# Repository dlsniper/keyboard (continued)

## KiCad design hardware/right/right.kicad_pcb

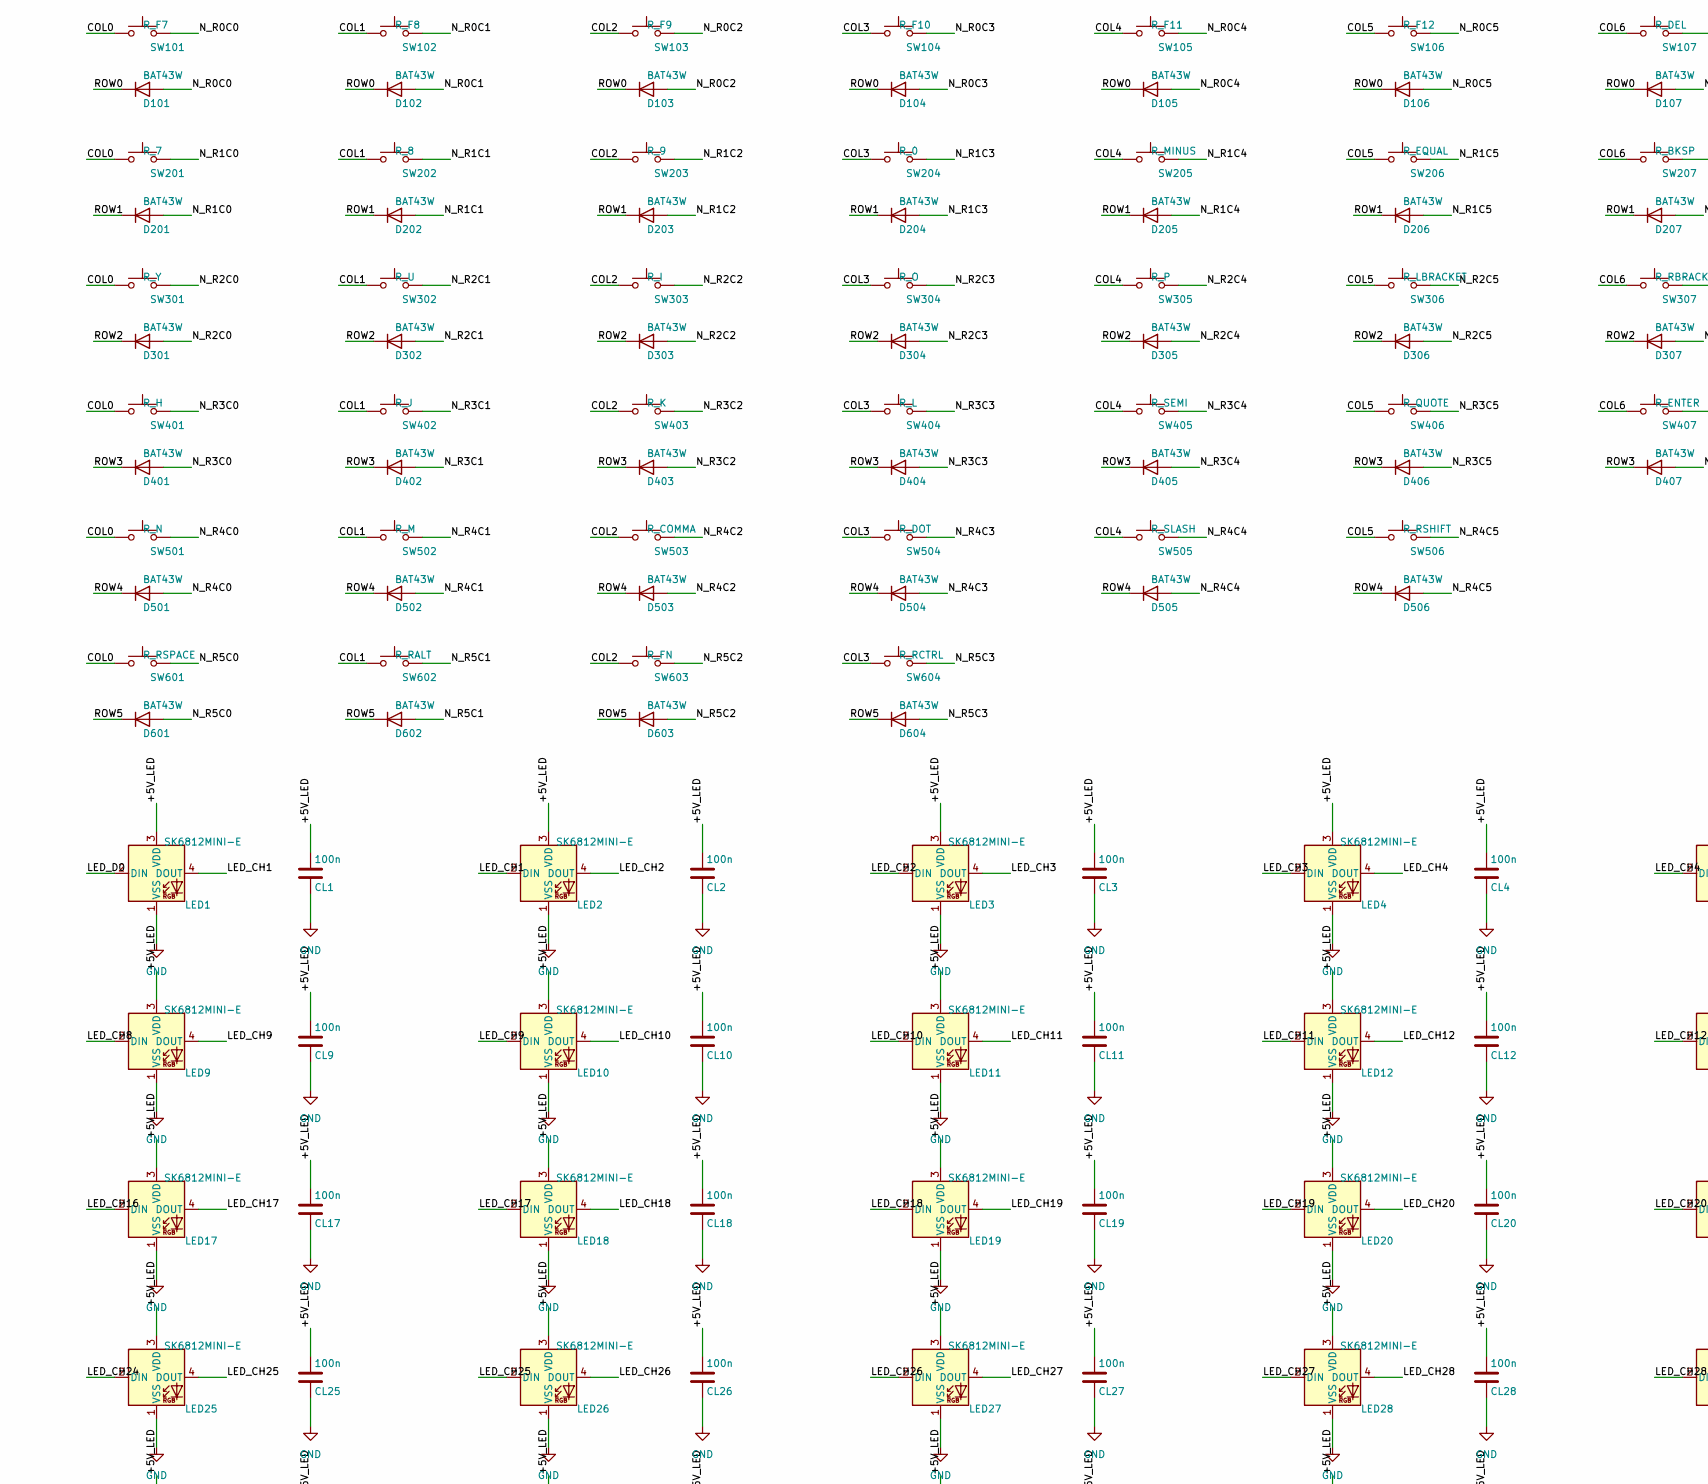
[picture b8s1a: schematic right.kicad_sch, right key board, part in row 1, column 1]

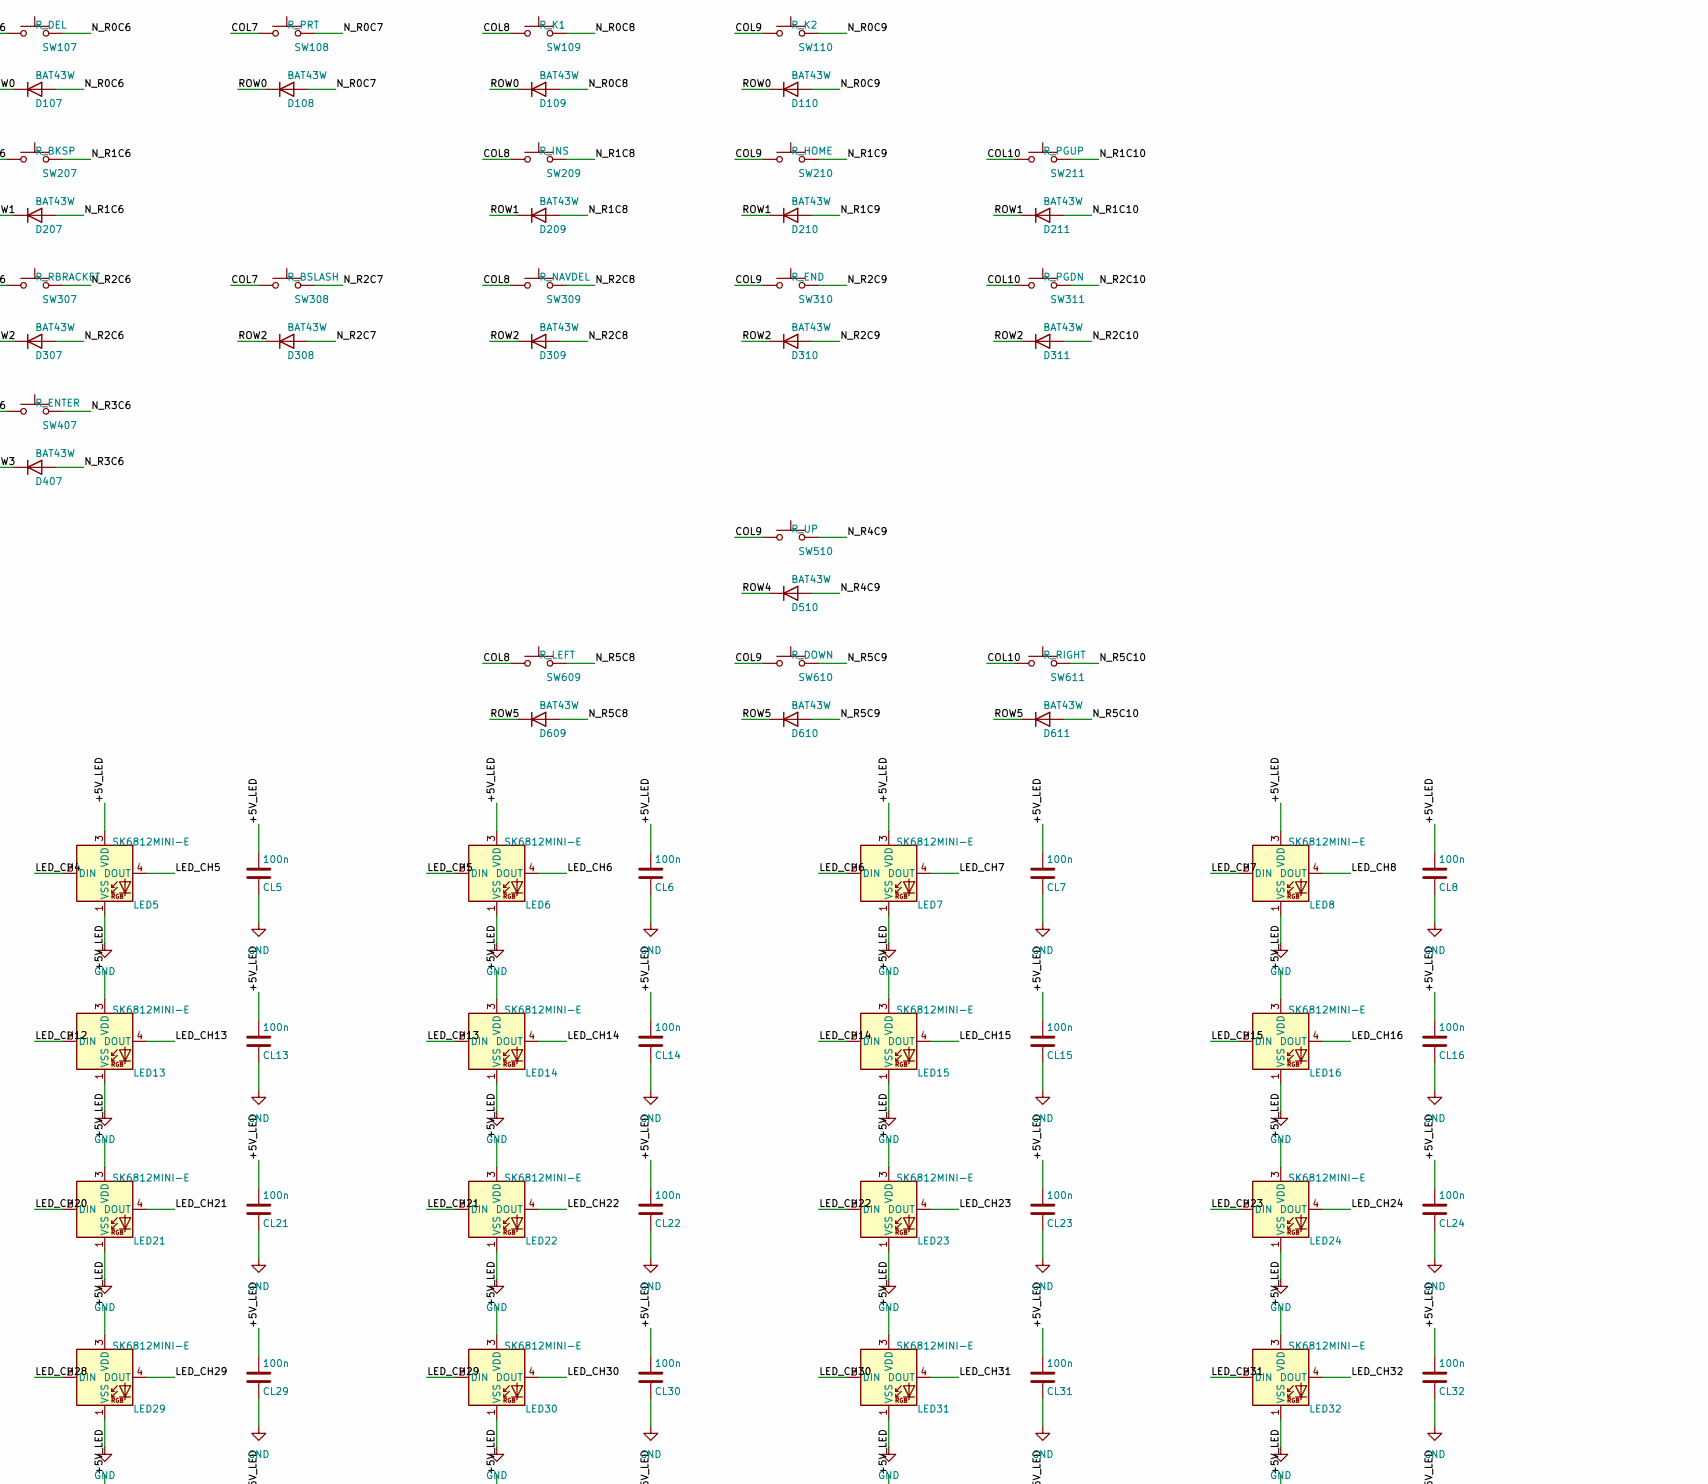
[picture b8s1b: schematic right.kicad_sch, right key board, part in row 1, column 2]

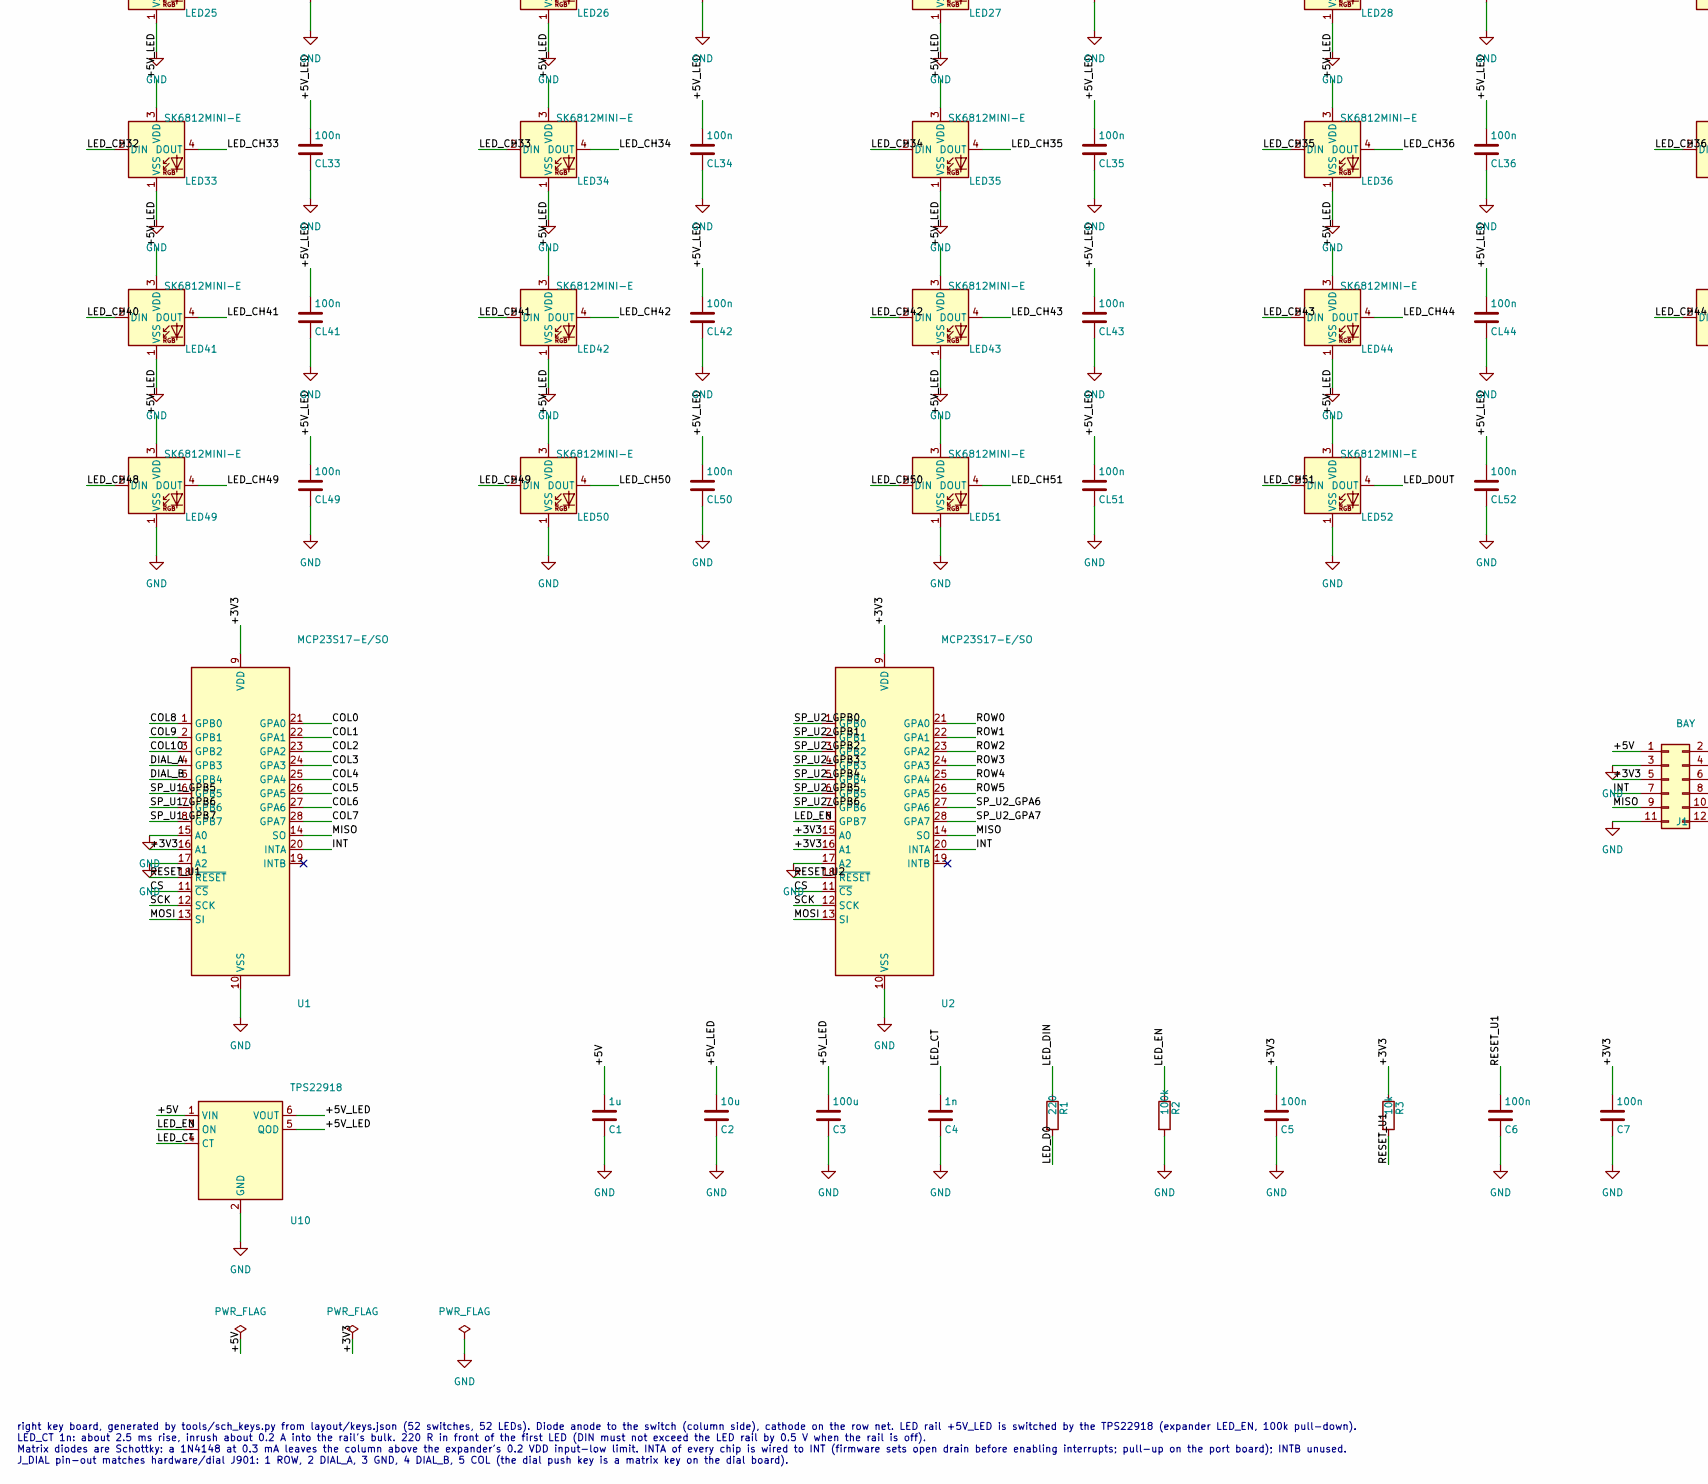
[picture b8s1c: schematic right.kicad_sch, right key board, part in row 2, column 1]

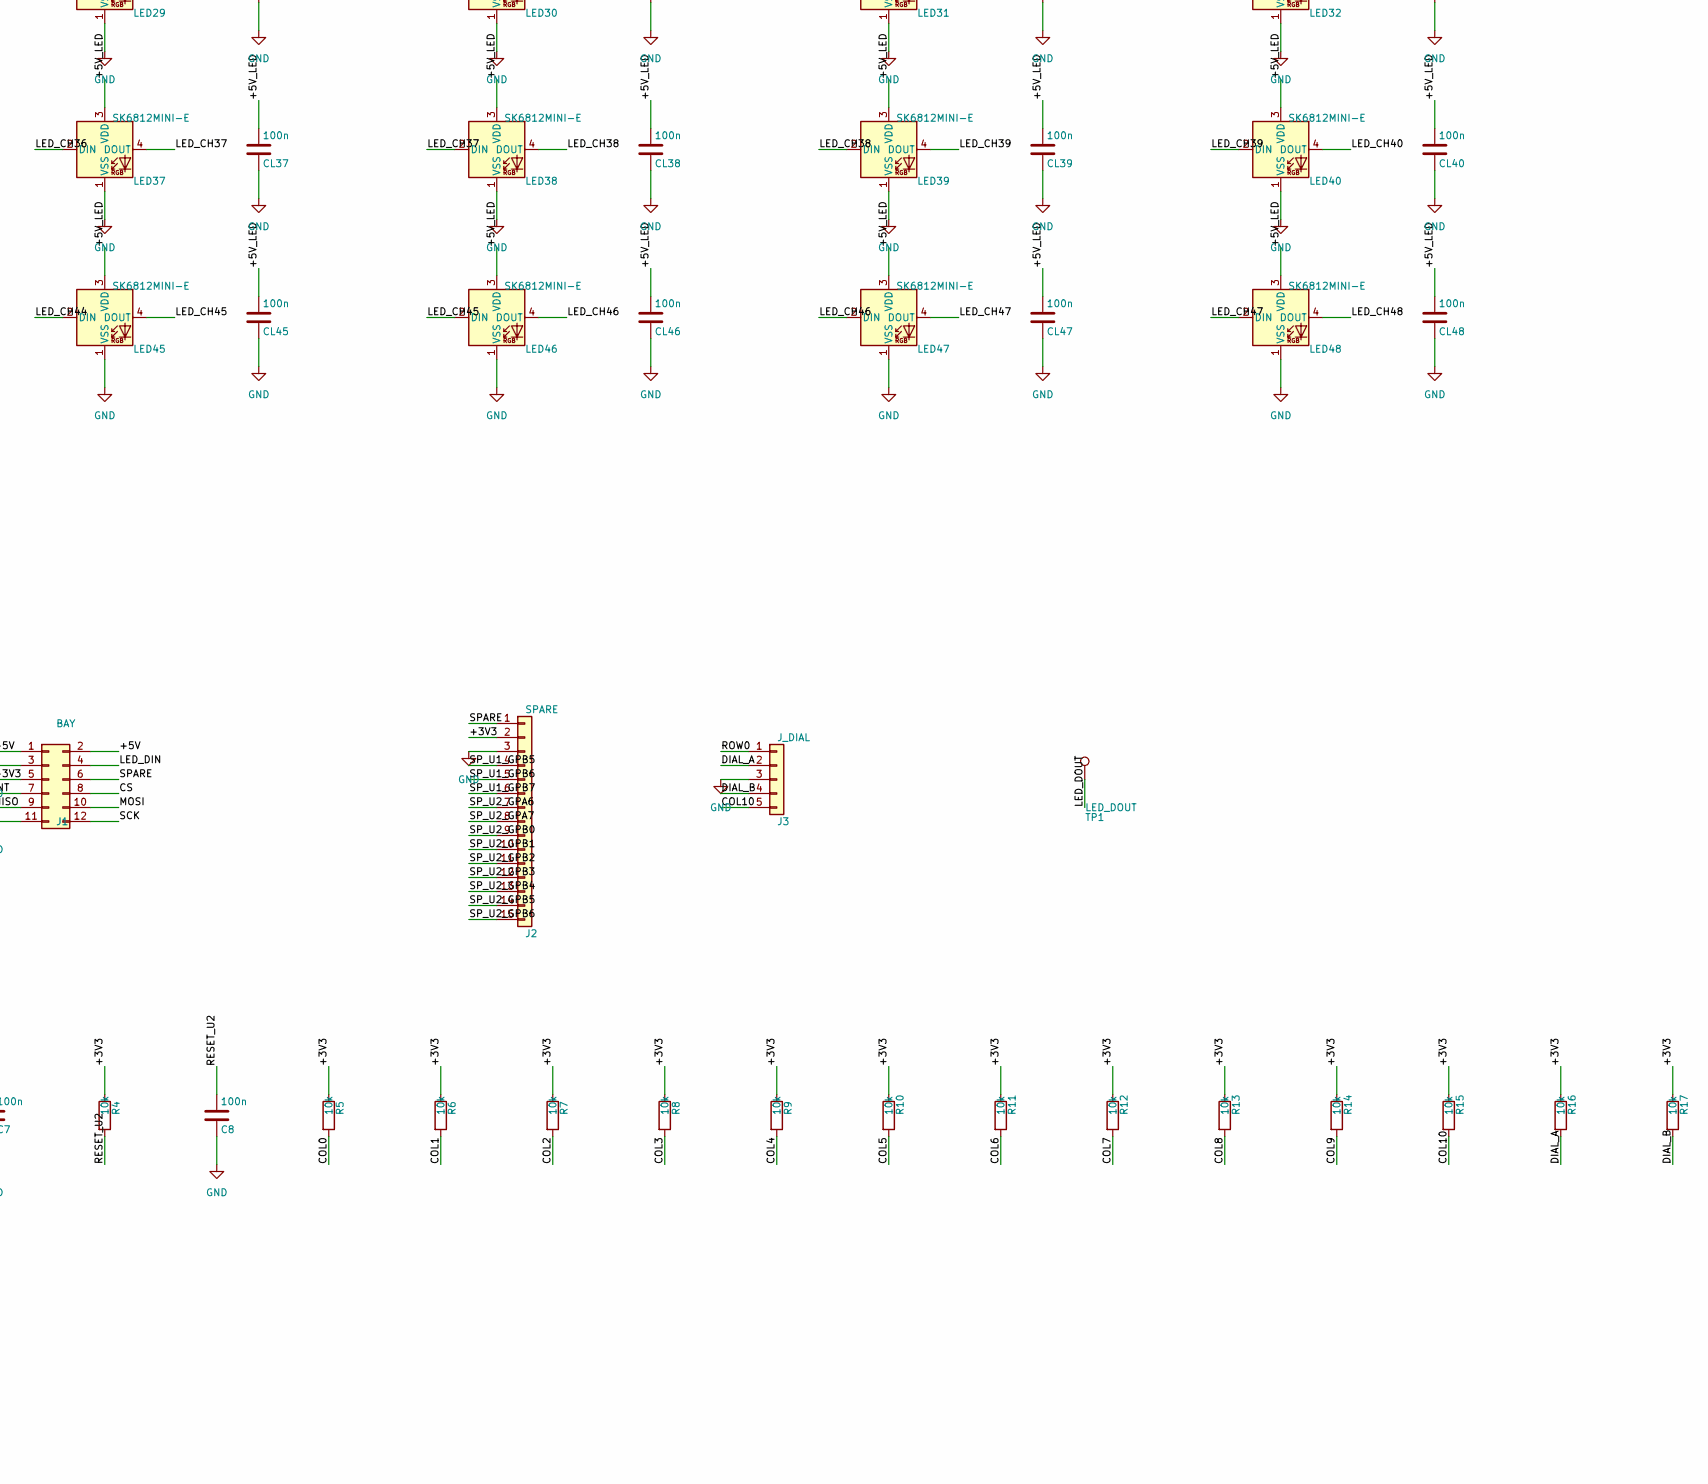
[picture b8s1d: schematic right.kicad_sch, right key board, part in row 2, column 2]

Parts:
C1: 1u; C_0805_2012Metric_Pad1.18x1.45mm_HandSolder; Voltage 16V
C2: 10u; C_0805_2012Metric_Pad1.18x1.45mm_HandSolder; Voltage 16V
C3: 100u; C_1210_3225Metric_Pad1.33x2.70mm_HandSolder; Voltage 10V
C4: 1n; C_0805_2012Metric_Pad1.18x1.45mm_HandSolder; Voltage 16V
C5, C6, C7, C8: 100n; C_0805_2012Metric_Pad1.18x1.45mm_HandSolder; Voltage 16V
CL1, CL2, CL3, CL4, CL5, CL6, CL7, CL8, CL9, CL10, CL11, CL12, CL13, CL14, CL15, CL16, CL17, CL18, CL19, CL20, CL21, CL22, CL23, CL24, CL25, CL26, CL27, CL28, CL29, CL30, CL31, CL32, CL33, CL34, CL35, CL36, CL37, CL38, CL39, CL40, CL41, CL42, CL43, CL44, CL45, CL46, CL47, CL48, CL49, CL50, CL51, CL52: 100n; C_0805_2012Metric_Pad1.18x1.45mm_HandSolder; Voltage 16V
D101, D102, D103, D104, D105, D106, D107, D108, D109, D110, D201, D202, D203, D204, D205, D206, D207, D209, D210, D211, D301, D302, D303, D304, D305, D306, D307, D308, D309, D310, D311, D401, D402, D403, D404, D405, D406, D407, D501, D502, D503, D504, D505, D506, D510, D601, D602, D603, D604, D609, D610, D611: BAT43W; D_SOD-123; MPN Schottky, SOD-123: BAT43W (VF 0.33 V ma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
J1: BAY; PinHeader_2x06_P2.54mm_Vertical; MPN generic 2x6 2.54 mm pin header
J2: SPARE; PinHeader_1x15_P2.54mm_Vertical; MPN generic 1xN 2.54 mm pin header
J3: J_DIAL; JST_GH_SM05B-GHS-TB_1x05-1MP_P1.25mm_Horizontal; MPN JST SM05B-GHS-TB
LED1, LED2, LED3, LED4, LED5, LED6, LED7, LED8, LED9, LED10, LED11, LED12, LED13, LED14, LED15, LED16, LED17, LED18, LED19, LED20, LED21, LED22, LED23, LED24, LED25, LED26, LED27, LED28, LED29, LED30, LED31, LED32, LED33, LED34, LED35, LED36, LED37, LED38, LED39, LED40, LED41, LED42, LED43, LED44, LED45, LED46, LED47, LED48, LED49, LED50, LED51, LED52: SK6812MINI-E; LED_SK6812MINI-E_3.2x2.8mm_P1.5mm_ReverseMount; MPN SK6812MINI-E
R1: 220; R_0805_2012Metric_Pad1.20x1.40mm_HandSolder; Tolerance 1%
R2: 100k; R_0805_2012Metric_Pad1.20x1.40mm_HandSolder; Tolerance 1%
R3, R4, R5, R6, R7, R8, R9, R10, R11, R12, R13, R14, R15, R16, R17: 10k; R_0805_2012Metric_Pad1.20x1.40mm_HandSolder; Tolerance 1%
SW101: R_F7; SW_Hotswap_Kailh_MX_1.00u; MPN Kailh CPG151101S11 hotswap socket
SW102: R_F8; SW_Hotswap_Kailh_MX_1.00u; MPN Kailh CPG151101S11 hotswap socket
SW103: R_F9; SW_Hotswap_Kailh_MX_1.00u; MPN Kailh CPG151101S11 hotswap socket
SW104: R_F10; SW_Hotswap_Kailh_MX_1.00u; MPN Kailh CPG151101S11 hotswap socket
SW105: R_F11; SW_Hotswap_Kailh_MX_1.00u; MPN Kailh CPG151101S11 hotswap socket
SW106: R_F12; SW_Hotswap_Kailh_MX_1.00u; MPN Kailh CPG151101S11 hotswap socket
SW107: R_DEL; SW_Hotswap_Kailh_MX_1.00u; MPN Kailh CPG151101S11 hotswap socket
SW108: R_PRT; SW_Hotswap_Kailh_MX_1.00u; MPN Kailh CPG151101S11 hotswap socket
SW109: R_K1; SW_Hotswap_Kailh_MX_1.00u; MPN Kailh CPG151101S11 hotswap socket
SW110: R_K2; SW_Hotswap_Kailh_MX_1.00u; MPN Kailh CPG151101S11 hotswap socket
SW201: R_7; SW_Hotswap_Kailh_MX_1.00u; MPN Kailh CPG151101S11 hotswap socket
SW202: R_8; SW_Hotswap_Kailh_MX_1.00u; MPN Kailh CPG151101S11 hotswap socket
SW203: R_9; SW_Hotswap_Kailh_MX_1.00u; MPN Kailh CPG151101S11 hotswap socket
SW204: R_0; SW_Hotswap_Kailh_MX_1.00u; MPN Kailh CPG151101S11 hotswap socket
SW205: R_MINUS; SW_Hotswap_Kailh_MX_1.00u; MPN Kailh CPG151101S11 hotswap socket
SW206: R_EQUAL; SW_Hotswap_Kailh_MX_1.00u; MPN Kailh CPG151101S11 hotswap socket
SW207: R_BKSP; SW_Hotswap_Kailh_MX_2.00u; MPN Kailh CPG151101S11 hotswap socket
SW209: R_INS; SW_Hotswap_Kailh_MX_1.00u; MPN Kailh CPG151101S11 hotswap socket
SW210: R_HOME; SW_Hotswap_Kailh_MX_1.00u; MPN Kailh CPG151101S11 hotswap socket
SW211: R_PGUP; SW_Hotswap_Kailh_MX_1.00u; MPN Kailh CPG151101S11 hotswap socket
SW301: R_Y; SW_Hotswap_Kailh_MX_1.00u; MPN Kailh CPG151101S11 hotswap socket
SW302: R_U; SW_Hotswap_Kailh_MX_1.00u; MPN Kailh CPG151101S11 hotswap socket
SW303: R_I; SW_Hotswap_Kailh_MX_1.00u; MPN Kailh CPG151101S11 hotswap socket
SW304: R_O; SW_Hotswap_Kailh_MX_1.00u; MPN Kailh CPG151101S11 hotswap socket
SW305: R_P; SW_Hotswap_Kailh_MX_1.00u; MPN Kailh CPG151101S11 hotswap socket
SW306: R_LBRACKET; SW_Hotswap_Kailh_MX_1.00u; MPN Kailh CPG151101S11 hotswap socket
SW307: R_RBRACKET; SW_Hotswap_Kailh_MX_1.00u; MPN Kailh CPG151101S11 hotswap socket
SW308: R_BSLASH; SW_Hotswap_Kailh_MX_1.50u; MPN Kailh CPG151101S11 hotswap socket
SW309: R_NAVDEL; SW_Hotswap_Kailh_MX_1.00u; MPN Kailh CPG151101S11 hotswap socket
SW310: R_END; SW_Hotswap_Kailh_MX_1.00u; MPN Kailh CPG151101S11 hotswap socket
SW311: R_PGDN; SW_Hotswap_Kailh_MX_1.00u; MPN Kailh CPG151101S11 hotswap socket
SW401: R_H; SW_Hotswap_Kailh_MX_1.00u; MPN Kailh CPG151101S11 hotswap socket
SW402: R_J; SW_Hotswap_Kailh_MX_1.00u; MPN Kailh CPG151101S11 hotswap socket
SW403: R_K; SW_Hotswap_Kailh_MX_1.00u; MPN Kailh CPG151101S11 hotswap socket
SW404: R_L; SW_Hotswap_Kailh_MX_1.00u; MPN Kailh CPG151101S11 hotswap socket
SW405: R_SEMI; SW_Hotswap_Kailh_MX_1.00u; MPN Kailh CPG151101S11 hotswap socket
SW406: R_QUOTE; SW_Hotswap_Kailh_MX_1.00u; MPN Kailh CPG151101S11 hotswap socket
SW407: R_ENTER; SW_Hotswap_Kailh_MX_2.25u; MPN Kailh CPG151101S11 hotswap socket
SW501: R_N; SW_Hotswap_Kailh_MX_1.00u; MPN Kailh CPG151101S11 hotswap socket
SW502: R_M; SW_Hotswap_Kailh_MX_1.00u; MPN Kailh CPG151101S11 hotswap socket
SW503: R_COMMA; SW_Hotswap_Kailh_MX_1.00u; MPN Kailh CPG151101S11 hotswap socket
SW504: R_DOT; SW_Hotswap_Kailh_MX_1.00u; MPN Kailh CPG151101S11 hotswap socket
SW505: R_SLASH; SW_Hotswap_Kailh_MX_1.00u; MPN Kailh CPG151101S11 hotswap socket
SW506: R_RSHIFT; SW_Hotswap_Kailh_MX_2.75u; MPN Kailh CPG151101S11 hotswap socket
SW510: R_UP; SW_Hotswap_Kailh_MX_1.00u; MPN Kailh CPG151101S11 hotswap socket
SW601: R_RSPACE; SW_Hotswap_Kailh_MX_2.75u; MPN Kailh CPG151101S11 hotswap socket
SW602: R_RALT; SW_Hotswap_Kailh_MX_1.75u; MPN Kailh CPG151101S11 hotswap socket
SW603: R_FN; SW_Hotswap_Kailh_MX_1.75u; MPN Kailh CPG151101S11 hotswap socket
SW604: R_RCTRL; SW_Hotswap_Kailh_MX_1.50u; MPN Kailh CPG151101S11 hotswap socket
SW609: R_LEFT; SW_Hotswap_Kailh_MX_1.00u; MPN Kailh CPG151101S11 hotswap socket
SW610: R_DOWN; SW_Hotswap_Kailh_MX_1.00u; MPN Kailh CPG151101S11 hotswap socket
SW611: R_RIGHT; SW_Hotswap_Kailh_MX_1.00u; MPN Kailh CPG151101S11 hotswap socket
TP1: LED_DOUT; TestPoint_Pad_D1.5mm
U1, U2: MCP23S17-E/SO; SOIC-28W_7.5x17.9mm_P1.27mm; MPN Microchip MCP23S17-E/SO
U10: TPS22918; TI_SOT-23-6_DBV0006A; MPN TI TPS22918DBVR

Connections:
/+3V3: C5.1, C7.1, J1.5, J2.2, R3.1, R4.1, R5.1, R6.1, R7.1, R8.1, R9.1, R10.1, R11.1, R12.1, R13.1, R14.1, R15.1, R16.1, R17.1, U1.9 (VDD), U1.16 (A1), U2.9 (VDD), U2.15 (A0), U2.16 (A1)
/+5V: C1.1, J1.1, J1.2, U10.1 (VIN)
/+5V_LED: C2.1, C3.1, CL1.1, CL2.1, CL3.1, CL4.1, CL5.1, CL6.1, CL7.1, CL8.1, CL9.1, CL10.1, CL11.1, CL12.1, CL13.1, CL14.1, CL15.1, CL16.1, CL17.1, CL18.1, CL19.1, CL20.1, CL21.1, CL22.1, CL23.1, CL24.1, CL25.1, CL26.1, CL27.1, CL28.1, CL29.1, CL30.1, CL31.1, CL32.1, CL33.1, CL34.1, CL35.1, CL36.1, CL37.1, CL38.1, CL39.1, CL40.1, CL41.1, CL42.1, CL43.1, CL44.1, CL45.1, CL46.1, CL47.1, CL48.1, CL49.1, CL50.1, CL51.1, CL52.1, LED1.3 (VDD), LED2.3 (VDD), LED3.3 (VDD), LED4.3 (VDD), LED5.3 (VDD), LED6.3 (VDD), LED7.3 (VDD), LED8.3 (VDD), LED9.3 (VDD), LED10.3 (VDD), LED11.3 (VDD), LED12.3 (VDD), LED13.3 (VDD), LED14.3 (VDD), LED15.3 (VDD), LED16.3 (VDD), LED17.3 (VDD), LED18.3 (VDD), LED19.3 (VDD), LED20.3 (VDD), LED21.3 (VDD), LED22.3 (VDD), LED23.3 (VDD), LED24.3 (VDD), LED25.3 (VDD), LED26.3 (VDD), LED27.3 (VDD), LED28.3 (VDD), LED29.3 (VDD), LED30.3 (VDD), LED31.3 (VDD), LED32.3 (VDD), LED33.3 (VDD), LED34.3 (VDD), LED35.3 (VDD), LED36.3 (VDD), LED37.3 (VDD), LED38.3 (VDD), LED39.3 (VDD), LED40.3 (VDD), LED41.3 (VDD), LED42.3 (VDD), LED43.3 (VDD), LED44.3 (VDD), LED45.3 (VDD), LED46.3 (VDD), LED47.3 (VDD), LED48.3 (VDD), LED49.3 (VDD), LED50.3 (VDD), LED51.3 (VDD), LED52.3 (VDD), U10.5 (QOD), U10.6 (VOUT)
/COL0: R5.2, SW101.1, SW201.1, SW301.1, SW401.1, SW501.1, SW601.1, U1.21 (GPA0)
/COL1: R6.2, SW102.1, SW202.1, SW302.1, SW402.1, SW502.1, SW602.1, U1.22 (GPA1)
/COL2: R7.2, SW103.1, SW203.1, SW303.1, SW403.1, SW503.1, SW603.1, U1.23 (GPA2)
/COL3: R8.2, SW104.1, SW204.1, SW304.1, SW404.1, SW504.1, SW604.1, U1.24 (GPA3)
/COL4: R9.2, SW105.1, SW205.1, SW305.1, SW405.1, SW505.1, U1.25 (GPA4)
/COL5: R10.2, SW106.1, SW206.1, SW306.1, SW406.1, SW506.1, U1.26 (GPA5)
/COL6: R11.2, SW107.1, SW207.1, SW307.1, SW407.1, U1.27 (GPA6)
/COL7: R12.2, SW108.1, SW308.1, U1.28 (GPA7)
/COL8: R13.2, SW109.1, SW209.1, SW309.1, SW609.1, U1.1 (GPB0)
/COL9: R14.2, SW110.1, SW210.1, SW310.1, SW510.1, SW610.1, U1.2 (GPB1)
/COL10: J3.5, R15.2, SW211.1, SW311.1, SW611.1, U1.3 (GPB2)
/CS: J1.8, U1.11 (~CS), U2.11 (~CS)
/DIAL_A: J3.2, R16.2, U1.4 (GPB3)
/DIAL_B: J3.4, R17.2, U1.5 (GPB4)
/INT: J1.7, U1.20 (INTA), U2.20 (INTA)
/LED_CH1: LED1.4 (DOUT), LED2.2 (DIN)
/LED_CH2: LED2.4 (DOUT), LED3.2 (DIN)
/LED_CH3: LED3.4 (DOUT), LED4.2 (DIN)
/LED_CH4: LED4.4 (DOUT), LED5.2 (DIN)
/LED_CH5: LED5.4 (DOUT), LED6.2 (DIN)
/LED_CH6: LED6.4 (DOUT), LED7.2 (DIN)
/LED_CH7: LED7.4 (DOUT), LED8.2 (DIN)
/LED_CH8: LED8.4 (DOUT), LED9.2 (DIN)
/LED_CH9: LED9.4 (DOUT), LED10.2 (DIN)
/LED_CH10: LED10.4 (DOUT), LED11.2 (DIN)
/LED_CH11: LED11.4 (DOUT), LED12.2 (DIN)
/LED_CH12: LED12.4 (DOUT), LED13.2 (DIN)
/LED_CH13: LED13.4 (DOUT), LED14.2 (DIN)
/LED_CH14: LED14.4 (DOUT), LED15.2 (DIN)
/LED_CH15: LED15.4 (DOUT), LED16.2 (DIN)
/LED_CH16: LED16.4 (DOUT), LED17.2 (DIN)
/LED_CH17: LED17.4 (DOUT), LED18.2 (DIN)
/LED_CH18: LED18.4 (DOUT), LED19.2 (DIN)
/LED_CH19: LED19.4 (DOUT), LED20.2 (DIN)
/LED_CH20: LED20.4 (DOUT), LED21.2 (DIN)
/LED_CH21: LED21.4 (DOUT), LED22.2 (DIN)
/LED_CH22: LED22.4 (DOUT), LED23.2 (DIN)
/LED_CH23: LED23.4 (DOUT), LED24.2 (DIN)
/LED_CH24: LED24.4 (DOUT), LED25.2 (DIN)
/LED_CH25: LED25.4 (DOUT), LED26.2 (DIN)
/LED_CH26: LED26.4 (DOUT), LED27.2 (DIN)
/LED_CH27: LED27.4 (DOUT), LED28.2 (DIN)
/LED_CH28: LED28.4 (DOUT), LED29.2 (DIN)
/LED_CH29: LED29.4 (DOUT), LED30.2 (DIN)
/LED_CH30: LED30.4 (DOUT), LED31.2 (DIN)
/LED_CH31: LED31.4 (DOUT), LED32.2 (DIN)
/LED_CH32: LED32.4 (DOUT), LED33.2 (DIN)
/LED_CH33: LED33.4 (DOUT), LED34.2 (DIN)
/LED_CH34: LED34.4 (DOUT), LED35.2 (DIN)
/LED_CH35: LED35.4 (DOUT), LED36.2 (DIN)
/LED_CH36: LED36.4 (DOUT), LED37.2 (DIN)
/LED_CH37: LED37.4 (DOUT), LED38.2 (DIN)
/LED_CH38: LED38.4 (DOUT), LED39.2 (DIN)
/LED_CH39: LED39.4 (DOUT), LED40.2 (DIN)
/LED_CH40: LED40.4 (DOUT), LED41.2 (DIN)
/LED_CH41: LED41.4 (DOUT), LED42.2 (DIN)
/LED_CH42: LED42.4 (DOUT), LED43.2 (DIN)
/LED_CH43: LED43.4 (DOUT), LED44.2 (DIN)
/LED_CH44: LED44.4 (DOUT), LED45.2 (DIN)
/LED_CH45: LED45.4 (DOUT), LED46.2 (DIN)
/LED_CH46: LED46.4 (DOUT), LED47.2 (DIN)
/LED_CH47: LED47.4 (DOUT), LED48.2 (DIN)
/LED_CH48: LED48.4 (DOUT), LED49.2 (DIN)
/LED_CH49: LED49.4 (DOUT), LED50.2 (DIN)
/LED_CH50: LED50.4 (DOUT), LED51.2 (DIN)
/LED_CH51: LED51.4 (DOUT), LED52.2 (DIN)
/LED_CT: C4.1, U10.4 (CT)
/LED_D0: LED1.2 (DIN), R1.2
/LED_DIN: J1.4, R1.1
/LED_DOUT: LED52.4 (DOUT), TP1.1
/LED_EN: R2.1, U2.8 (GPB7), U10.3 (ON)
/MISO: J1.9, U1.14 (SO), U2.14 (SO)
/MOSI: J1.10, U1.13 (SI), U2.13 (SI)
/N_R0C0: D101.2 (A), SW101.2
/N_R0C1: D102.2 (A), SW102.2
/N_R0C2: D103.2 (A), SW103.2
/N_R0C3: D104.2 (A), SW104.2
/N_R0C4: D105.2 (A), SW105.2
/N_R0C5: D106.2 (A), SW106.2
/N_R0C6: D107.2 (A), SW107.2
/N_R0C7: D108.2 (A), SW108.2
/N_R0C8: D109.2 (A), SW109.2
/N_R0C9: D110.2 (A), SW110.2
/N_R1C0: D201.2 (A), SW201.2
/N_R1C1: D202.2 (A), SW202.2
/N_R1C2: D203.2 (A), SW203.2
/N_R1C3: D204.2 (A), SW204.2
/N_R1C4: D205.2 (A), SW205.2
/N_R1C5: D206.2 (A), SW206.2
/N_R1C6: D207.2 (A), SW207.2
/N_R1C8: D209.2 (A), SW209.2
/N_R1C9: D210.2 (A), SW210.2
/N_R1C10: D211.2 (A), SW211.2
/N_R2C0: D301.2 (A), SW301.2
/N_R2C1: D302.2 (A), SW302.2
/N_R2C2: D303.2 (A), SW303.2
/N_R2C3: D304.2 (A), SW304.2
/N_R2C4: D305.2 (A), SW305.2
/N_R2C5: D306.2 (A), SW306.2
/N_R2C6: D307.2 (A), SW307.2
/N_R2C7: D308.2 (A), SW308.2
/N_R2C8: D309.2 (A), SW309.2
/N_R2C9: D310.2 (A), SW310.2
/N_R2C10: D311.2 (A), SW311.2
/N_R3C0: D401.2 (A), SW401.2
/N_R3C1: D402.2 (A), SW402.2
/N_R3C2: D403.2 (A), SW403.2
/N_R3C3: D404.2 (A), SW404.2
/N_R3C4: D405.2 (A), SW405.2
/N_R3C5: D406.2 (A), SW406.2
/N_R3C6: D407.2 (A), SW407.2
/N_R4C0: D501.2 (A), SW501.2
/N_R4C1: D502.2 (A), SW502.2
/N_R4C2: D503.2 (A), SW503.2
/N_R4C3: D504.2 (A), SW504.2
/N_R4C4: D505.2 (A), SW505.2
/N_R4C5: D506.2 (A), SW506.2
/N_R4C9: D510.2 (A), SW510.2
/N_R5C0: D601.2 (A), SW601.2
/N_R5C1: D602.2 (A), SW602.2
/N_R5C2: D603.2 (A), SW603.2
/N_R5C3: D604.2 (A), SW604.2
/N_R5C8: D609.2 (A), SW609.2
/N_R5C9: D610.2 (A), SW610.2
/N_R5C10: D611.2 (A), SW611.2
/RESET_U1: C6.1, R3.2, U1.18 (~RESET)
/RESET_U2: C8.1, R4.2, U2.18 (~RESET)
/ROW0: D101.1 (K), D102.1 (K), D103.1 (K), D104.1 (K), D105.1 (K), D106.1 (K), D107.1 (K), D108.1 (K), D109.1 (K), D110.1 (K), J3.1, U2.21 (GPA0)
/ROW1: D201.1 (K), D202.1 (K), D203.1 (K), D204.1 (K), D205.1 (K), D206.1 (K), D207.1 (K), D209.1 (K), D210.1 (K), D211.1 (K), U2.22 (GPA1)
/ROW2: D301.1 (K), D302.1 (K), D303.1 (K), D304.1 (K), D305.1 (K), D306.1 (K), D307.1 (K), D308.1 (K), D309.1 (K), D310.1 (K), D311.1 (K), U2.23 (GPA2)
/ROW3: D401.1 (K), D402.1 (K), D403.1 (K), D404.1 (K), D405.1 (K), D406.1 (K), D407.1 (K), U2.24 (GPA3)
/ROW4: D501.1 (K), D502.1 (K), D503.1 (K), D504.1 (K), D505.1 (K), D506.1 (K), D510.1 (K), U2.25 (GPA4)
/ROW5: D601.1 (K), D602.1 (K), D603.1 (K), D604.1 (K), D609.1 (K), D610.1 (K), D611.1 (K), U2.26 (GPA5)
/SCK: J1.12, U1.12 (SCK), U2.12 (SCK)
/SPARE: J1.6, J2.1
/SP_U1_GPB5: J2.4, U1.6 (GPB5)
/SP_U1_GPB6: J2.5, U1.7 (GPB6)
/SP_U1_GPB7: J2.6, U1.8 (GPB7)
/SP_U2_GPA6: J2.7, U2.27 (GPA6)
/SP_U2_GPA7: J2.8, U2.28 (GPA7)
/SP_U2_GPB0: J2.9, U2.1 (GPB0)
/SP_U2_GPB1: J2.10, U2.2 (GPB1)
/SP_U2_GPB2: J2.11, U2.3 (GPB2)
/SP_U2_GPB3: J2.12, U2.4 (GPB3)
/SP_U2_GPB4: J2.13, U2.5 (GPB4)
/SP_U2_GPB5: J2.14, U2.6 (GPB5)
/SP_U2_GPB6: J2.15, U2.7 (GPB6)
GND: C1.2, C2.2, C3.2, C4.2, C5.2, C6.2, C7.2, C8.2, CL1.2, CL2.2, CL3.2, CL4.2, CL5.2, CL6.2, CL7.2, CL8.2, CL9.2, CL10.2, CL11.2, CL12.2, CL13.2, CL14.2, CL15.2, CL16.2, CL17.2, CL18.2, CL19.2, CL20.2, CL21.2, CL22.2, CL23.2, CL24.2, CL25.2, CL26.2, CL27.2, CL28.2, CL29.2, CL30.2, CL31.2, CL32.2, CL33.2, CL34.2, CL35.2, CL36.2, CL37.2, CL38.2, CL39.2, CL40.2, CL41.2, CL42.2, CL43.2, CL44.2, CL45.2, CL46.2, CL47.2, CL48.2, CL49.2, CL50.2, CL51.2, CL52.2, J1.3, J1.11, J2.3, J3.3, LED1.1 (VSS), LED2.1 (VSS), LED3.1 (VSS), LED4.1 (VSS), LED5.1 (VSS), LED6.1 (VSS), LED7.1 (VSS), LED8.1 (VSS), LED9.1 (VSS), LED10.1 (VSS), LED11.1 (VSS), LED12.1 (VSS), LED13.1 (VSS), LED14.1 (VSS), LED15.1 (VSS), LED16.1 (VSS), LED17.1 (VSS), LED18.1 (VSS), LED19.1 (VSS), LED20.1 (VSS), LED21.1 (VSS), LED22.1 (VSS), LED23.1 (VSS), LED24.1 (VSS), LED25.1 (VSS), LED26.1 (VSS), LED27.1 (VSS), LED28.1 (VSS), LED29.1 (VSS), LED30.1 (VSS), LED31.1 (VSS), LED32.1 (VSS), LED33.1 (VSS), LED34.1 (VSS), LED35.1 (VSS), LED36.1 (VSS), LED37.1 (VSS), LED38.1 (VSS), LED39.1 (VSS), LED40.1 (VSS), LED41.1 (VSS), LED42.1 (VSS), LED43.1 (VSS), LED44.1 (VSS), LED45.1 (VSS), LED46.1 (VSS), LED47.1 (VSS), LED48.1 (VSS), LED49.1 (VSS), LED50.1 (VSS), LED51.1 (VSS), LED52.1 (VSS), R2.2, U1.10 (VSS), U1.15 (A0), U1.17 (A2), U2.10 (VSS), U2.17 (A2), U10.2 (GND)

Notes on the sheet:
right key board, generated by tools/sch_keys.py from layout/keys.json (52 switches, 52 LEDs). Diode anode to the switch (column side), cathode on the row net. LED rail +5V_LED is switched by the TPS22918 (expander LED_EN, 100k pull-down). LED_CT 1n: about 2.5 ms rise, inrush about 0.2 A into the ra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

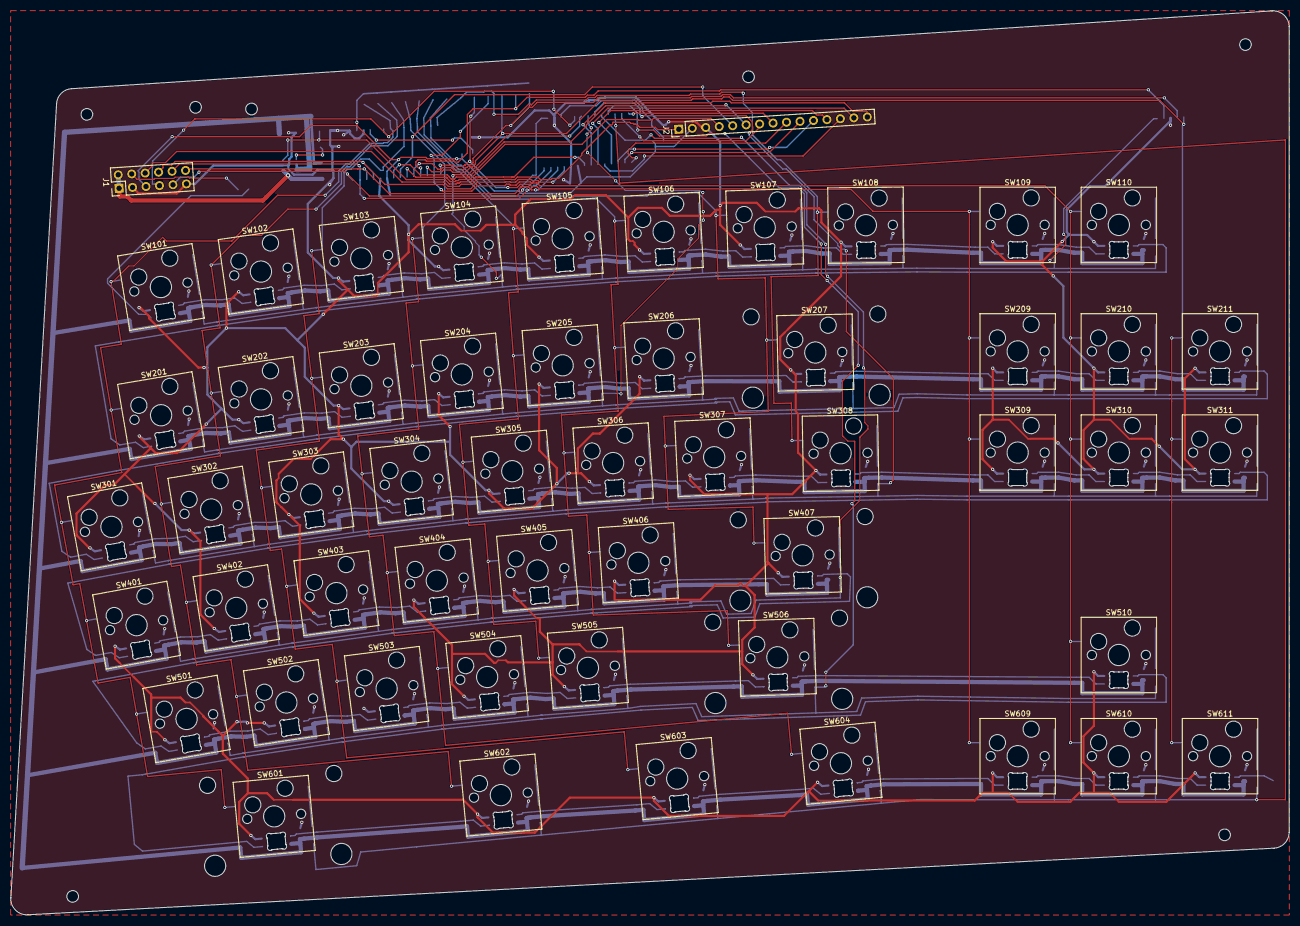
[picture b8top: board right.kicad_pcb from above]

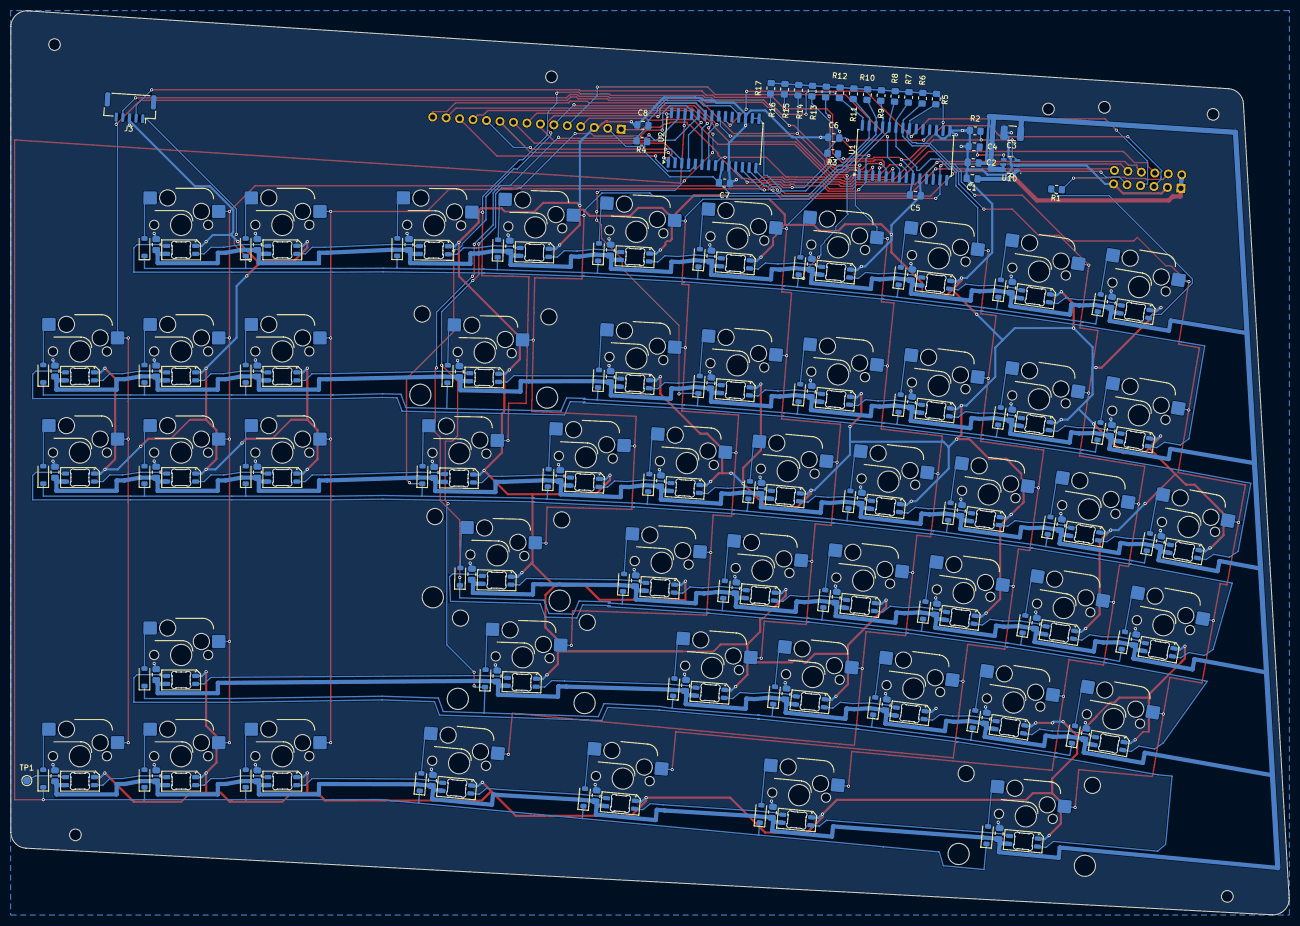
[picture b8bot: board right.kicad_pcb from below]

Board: 2 copper layers, 240.6 x 170.2 mm, 251 parts (186 on the bottom side), 151 nets.

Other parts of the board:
H5, H6, H7, H8, H9, H10, H11: MountingHole_2.2mm_M2
ST1, ST2, ST3, ST4: Stabilizer_Cherry_MX_2.00u
